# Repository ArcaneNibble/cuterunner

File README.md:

# Cuterunner

Simple CoolRunner-II dev boards

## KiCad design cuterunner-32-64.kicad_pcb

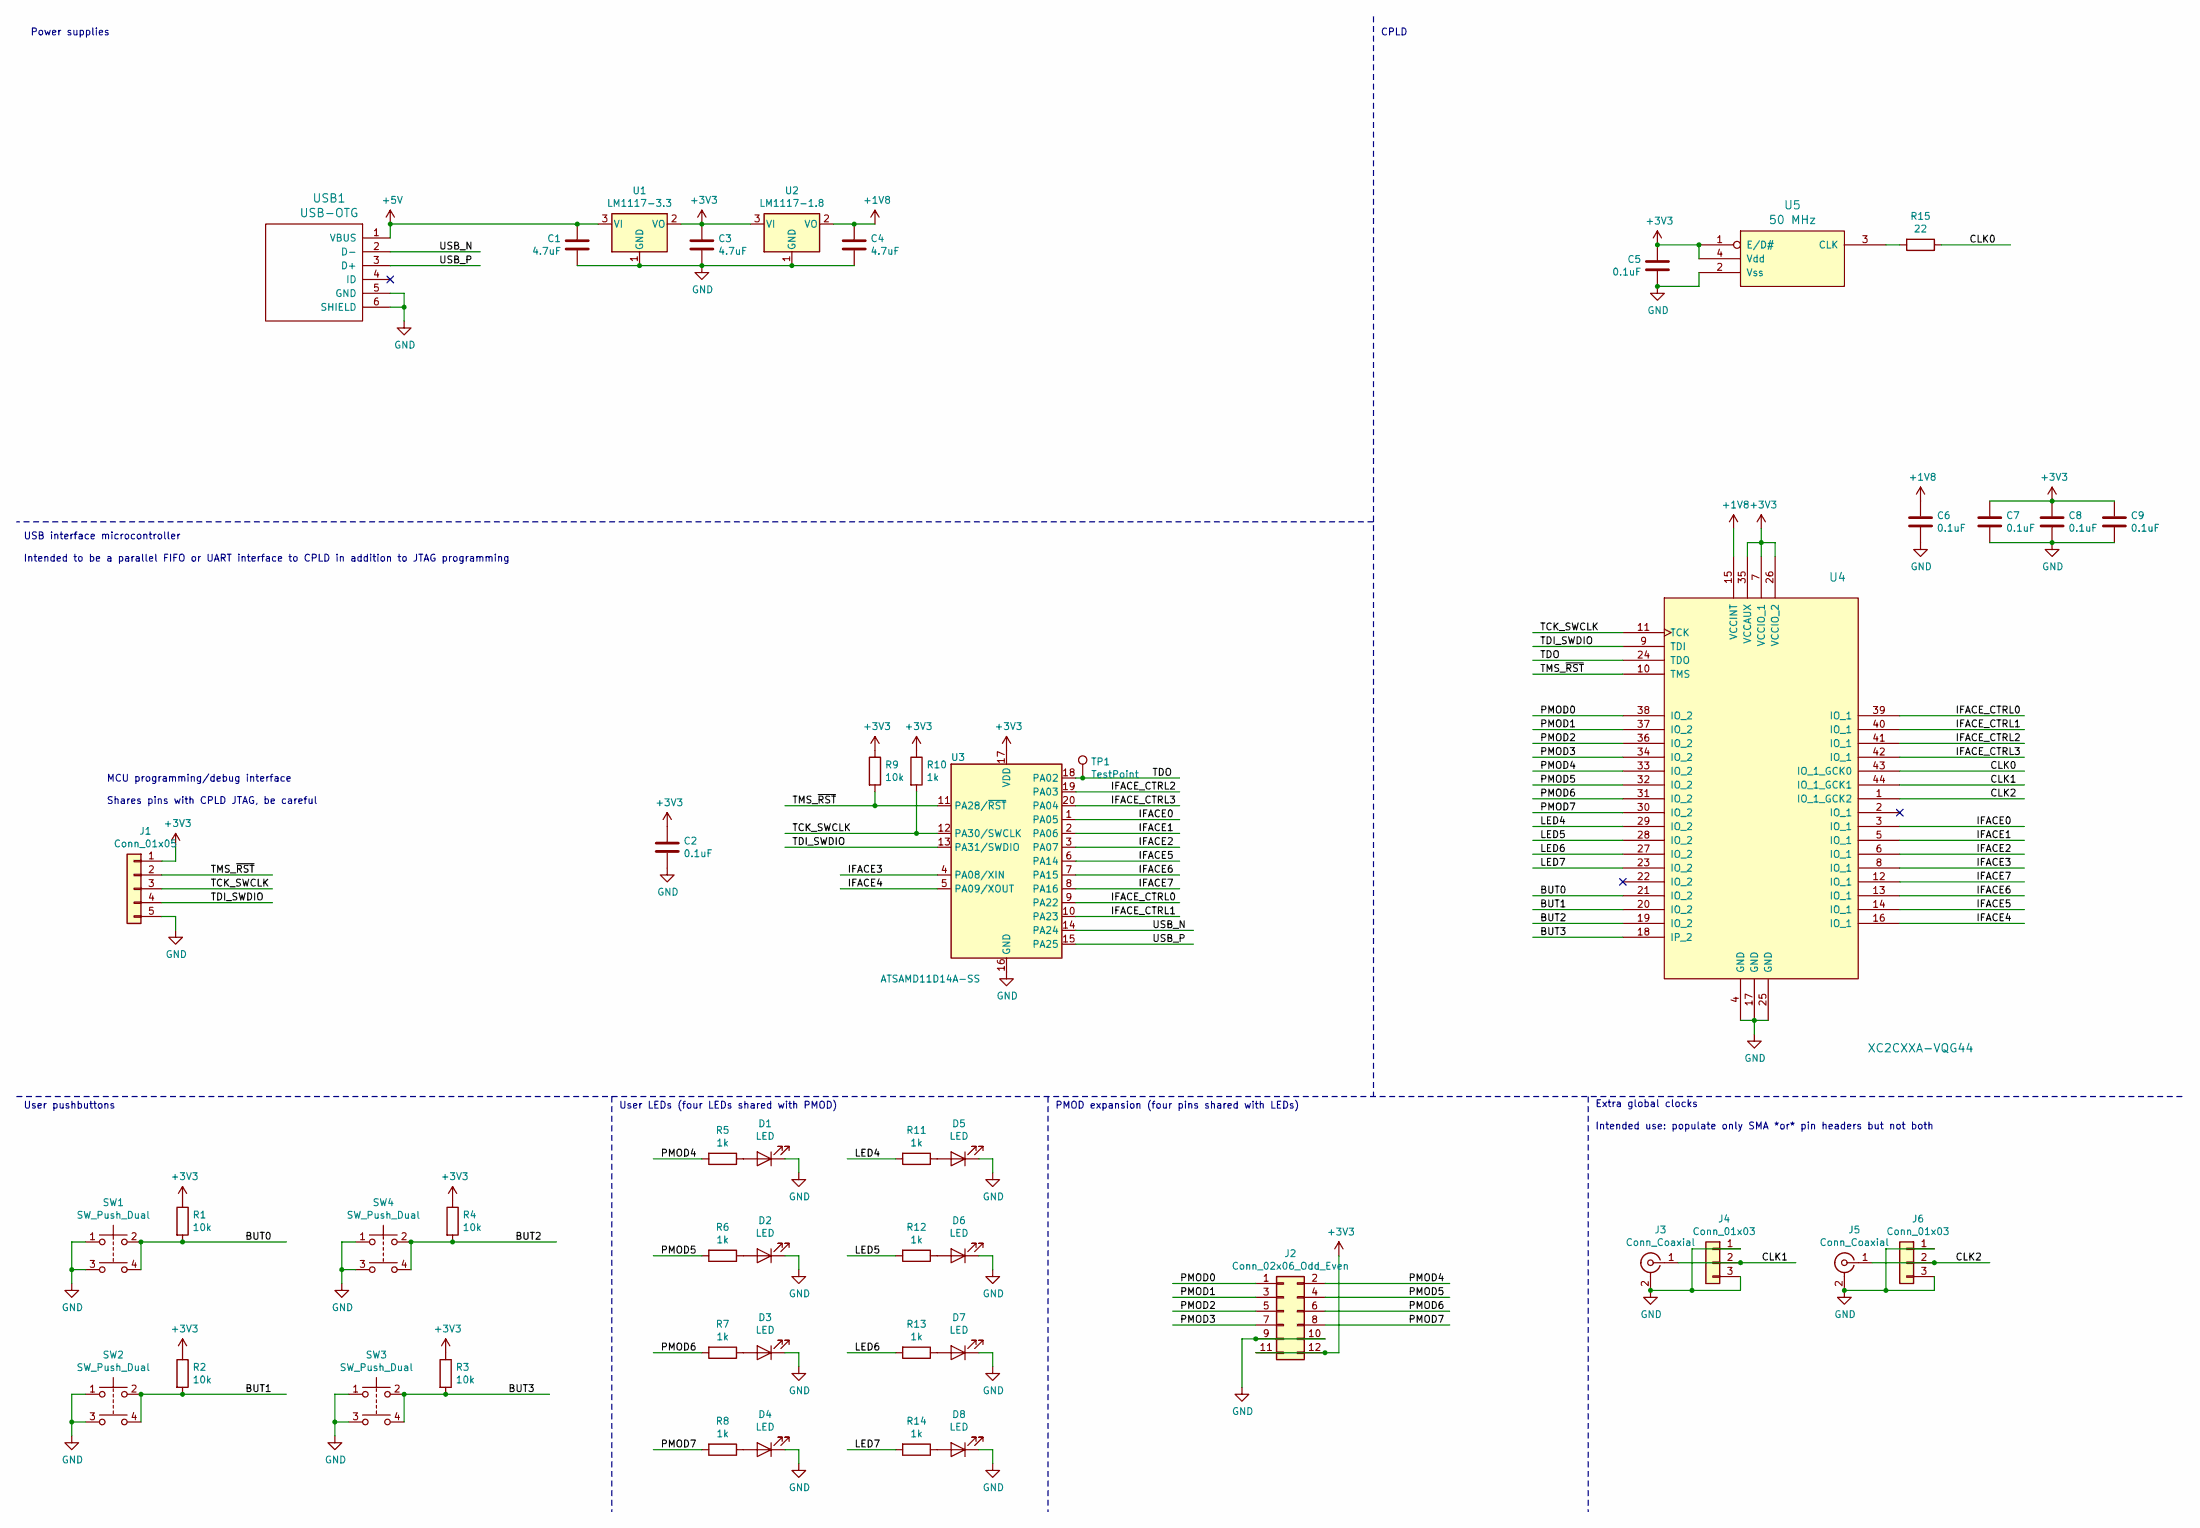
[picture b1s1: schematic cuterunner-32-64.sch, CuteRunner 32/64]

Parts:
C1, C3, C4: 4.7uF; C_1206_3216Metric_Pad1.42x1.75mm_HandSolder
C2, C5, C6, C7, C8, C9: 0.1uF; C_0805_2012Metric_Pad1.15x1.40mm_HandSolder
D1, D2, D3, D4, D5, D6, D7, D8: LED; LED_0805_2012Metric_Pad1.15x1.40mm_HandSolder
J1: Conn_01x05; PinHeader_1x05_P2.54mm_Vertical
J2: Conn_02x06_Odd_Even; PinHeader_2x06_P2.54mm_Horizontal
J3, J5: Conn_Coaxial; CONN_SMA_PTH
J4, J6: Conn_01x03; PinHeader_1x03_P2.54mm_Vertical
R1, R2, R3, R4, R9: 10k; R_0805_2012Metric_Pad1.15x1.40mm_HandSolder
R5, R6, R7, R8, R10, R11, R12, R13, R14: 1k; R_0805_2012Metric_Pad1.15x1.40mm_HandSolder
R15: 22; R_0805_2012Metric_Pad1.15x1.40mm_HandSolder
SW1, SW2, SW3, SW4: SW_Push_Dual; SW_TH_Tactile_Omron_B3F-10xx
TP1: TestPoint; PinHeader_1x01_P2.54mm_Vertical
U1: LM1117-3.3; SOT-223-3_TabPin2
U2: LM1117-1.8; SOT-223-3_TabPin2
U3: ATSAMD11D14A-SS; SOIC-20W_7.5x12.8mm_P1.27mm
U4: XC2CXXA-VQG44; QFP_44_0.8MM
U5: 50 MHz; OSCILLATOR_3.2x2.5
USB1: USB-OTG; USB-MICRO-AB

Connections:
+1V8: C4.1, C6.1, U2.2 (VO), U4.15 (VCCINT)
+3V3: C2.1, C3.1, C5.2, C7.1, C8.1, C9.1, J1.1, J2.11, J2.12, R1.1, R2.1, R3.1, R4.1, R9.1, R10.1, U1.2 (VO), U2.3 (VI), U3.17 (VDD), U4.7 (VCCIO_1), U4.26 (VCCIO_2), U4.35 (VCCAUX), U5.1 (E/D#), U5.4 (Vdd)
+5V: C1.2, U1.3 (VI), USB1.1 (VBUS)
/BUT0: R1.2, SW1.2, SW1.4, U4.21 (IO_2)
/BUT1: R2.2, SW2.2, SW2.4, U4.20 (IO_2)
/BUT2: R4.2, SW4.2, SW4.4, U4.19 (IO_2)
/BUT3: R3.2, SW3.2, SW3.4, U4.18 (IP_2)
/CLK0: R15.1, U4.43 (IO_1_GCK0)
/CLK1: J3.1 (In), J4.2, U4.44 (IO_1_GCK1)
/CLK2: J5.1 (In), J6.2, U4.1 (IO_1_GCK2)
/IFACE0: U3.1 (PA05), U4.3 (IO_1)
/IFACE1: U3.2 (PA06), U4.5 (IO_1)
/IFACE2: U3.3 (PA07), U4.6 (IO_1)
/IFACE3: U3.4 (PA08/XIN), U4.8 (IO_1)
/IFACE4: U3.5 (PA09/XOUT), U4.16 (IO_1)
/IFACE5: U3.6 (PA14), U4.14 (IO_1)
/IFACE6: U3.7 (PA15), U4.13 (IO_1)
/IFACE7: U3.8 (PA16), U4.12 (IO_1)
/IFACE_CTRL0: U3.9 (PA22), U4.39 (IO_1)
/IFACE_CTRL1: U3.10 (PA23), U4.40 (IO_1)
/IFACE_CTRL2: U3.19 (PA03), U4.41 (IO_1)
/IFACE_CTRL3: U3.20 (PA04), U4.42 (IO_1)
/LED4: R11.2, U4.29 (IO_2)
/LED5: R12.2, U4.28 (IO_2)
/LED6: R13.2, U4.27 (IO_2)
/LED7: R14.2, U4.23 (IO_2)
/PMOD0: J2.1, U4.38 (IO_2)
/PMOD1: J2.3, U4.37 (IO_2)
/PMOD2: J2.5, U4.36 (IO_2)
/PMOD3: J2.7, U4.34 (IO_2)
/PMOD4: J2.2, R5.2, U4.33 (IO_2)
/PMOD5: J2.4, R6.2, U4.32 (IO_2)
/PMOD6: J2.6, R7.2, U4.31 (IO_2)
/PMOD7: J2.8, R8.2, U4.30 (IO_2)
/TCK_SWCLK: J1.3, R10.2, U3.12 (PA30/SWCLK), U4.11 (TCK)
/TDI_SWDIO: J1.4, U3.13 (PA31/SWDIO), U4.9 (TDI)
/TDO: TP1.1, U3.18 (PA02), U4.24 (TDO)
/TMS_~RST: J1.2, R9.2, U3.11 (PA28/~RST), U4.10 (TMS)
/USB_N: U3.14 (PA24), USB1.2 (D-)
/USB_P: U3.15 (PA25), USB1.3 (D+)
GND: C1.1, C2.2, C3.2, C4.2, C5.1, C6.2, C7.2, C8.2, C9.2, D1.1 (K), D2.1 (K), D3.1 (K), D4.1 (K), D5.1 (K), D6.1 (K), D7.1 (K), D8.1 (K), J1.5, J2.9, J2.10, J3.2 (Ext), J4.1, J4.3, J5.2 (Ext), J6.1, J6.3, SW1.1, SW1.3, SW2.1, SW2.3, SW3.1, SW3.3, SW4.1, SW4.3, U1.1 (GND), U2.1 (GND), U3.16 (GND), U4.4 (GND), U4.17 (GND), U4.25 (GND), U5.2 (Vss), USB1.5 (GND), USB1.6 (SHIELD), USB1.7 (SHIELD), USB1.8 (SHIELD), USB1.9 (SHIELD), USB1.10 (SHIELD), USB1.11 (SHIELD)
unnamed: D1.2 (A), R5.1
unnamed: D2.2 (A), R6.1
unnamed: D3.2 (A), R7.1
unnamed: D4.2 (A), R8.1
unnamed: D5.2 (A), R11.1
unnamed: D6.2 (A), R12.1
unnamed: D7.2 (A), R13.1
unnamed: D8.2 (A), R14.1
unnamed: R15.2, U5.3 (CLK)

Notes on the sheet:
User pushbuttons
User LEDs (four LEDs shared with PMOD)
PMOD expansion (four pins shared with LEDs)
Extra global clocks Intended use: populate only SMA *or* pin headers but not both
CPLD
USB interface microcontroller Intended to be a parallel FIFO or UART interface to CPLD in addition to JTAG programming
MCU programming/debug interface Shares pins with CPLD JTAG, be careful
Power supplies

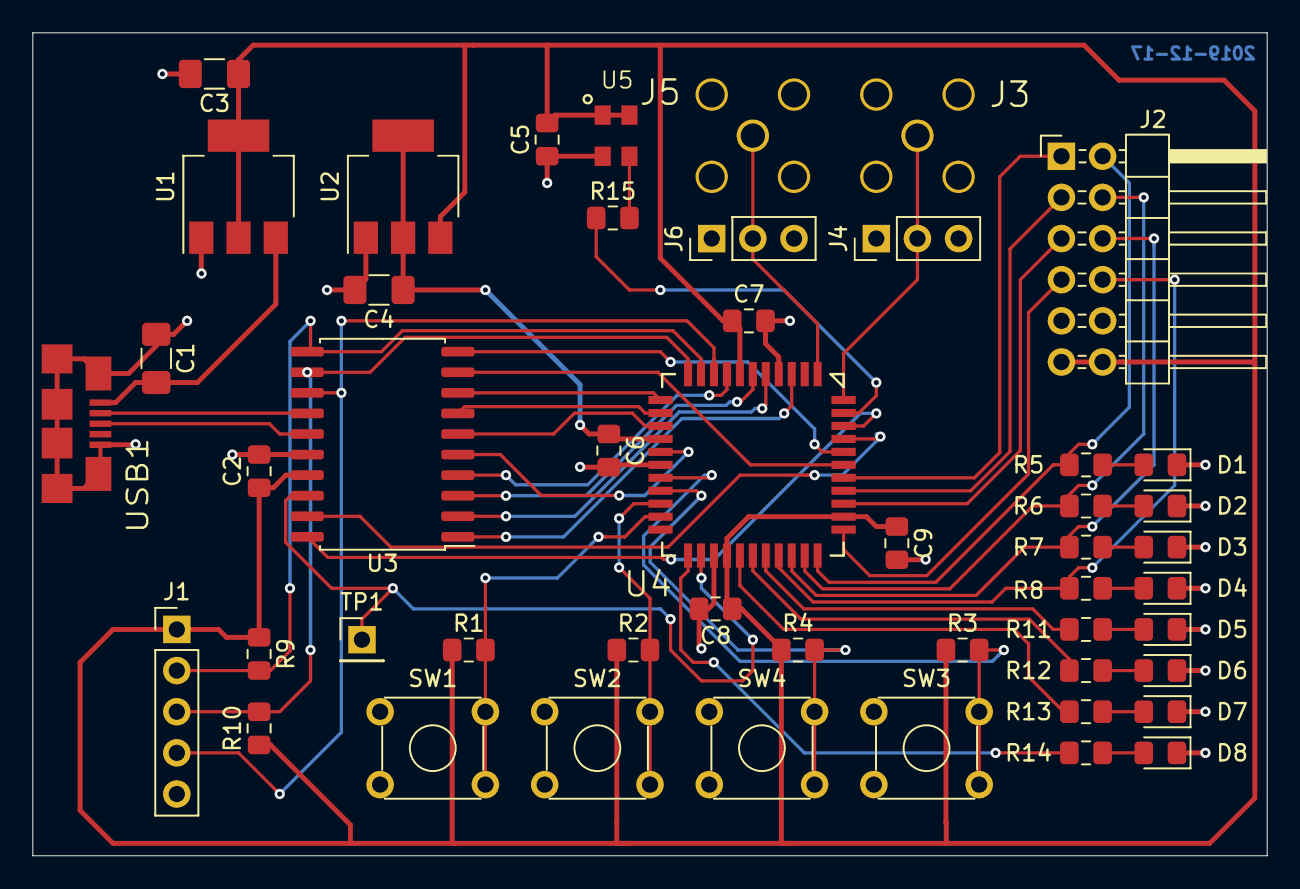
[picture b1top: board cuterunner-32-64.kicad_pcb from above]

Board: 2 copper layers, 76.2 x 50.8 mm, 49 parts (0 on the bottom side), 50 nets.

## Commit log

2019-12-17 Empty project
2019-12-17 Rename files
2019-12-17 Throw on most parts
2019-12-17 Microcontroller part
2019-12-17 Many CPLD parts
2019-12-17 Added osc
2019-12-17 Schematic mostly done
2019-12-17 Assign footprints
2019-12-17 Apparently I have to rename the project too
2019-12-17 Very rough placement
2019-12-17 Placement of components
2019-12-17 Very sloppy first pass routing
2019-12-17 Good enough trace routing to ship
2019-12-17 Ship it
2019-12-17 Misc
2019-12-17 Silk fix
